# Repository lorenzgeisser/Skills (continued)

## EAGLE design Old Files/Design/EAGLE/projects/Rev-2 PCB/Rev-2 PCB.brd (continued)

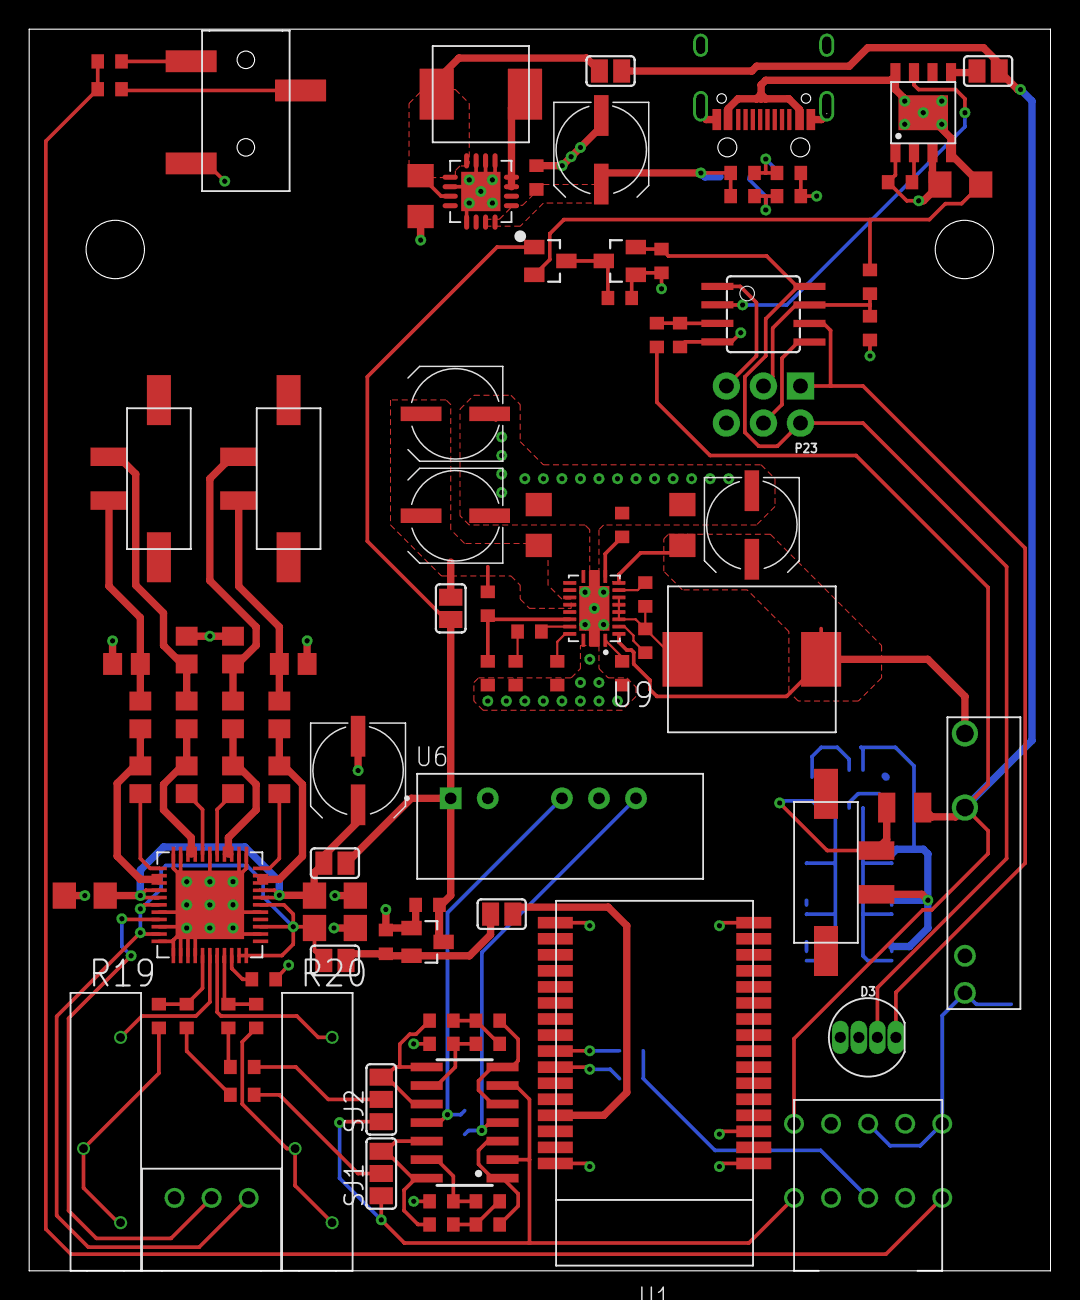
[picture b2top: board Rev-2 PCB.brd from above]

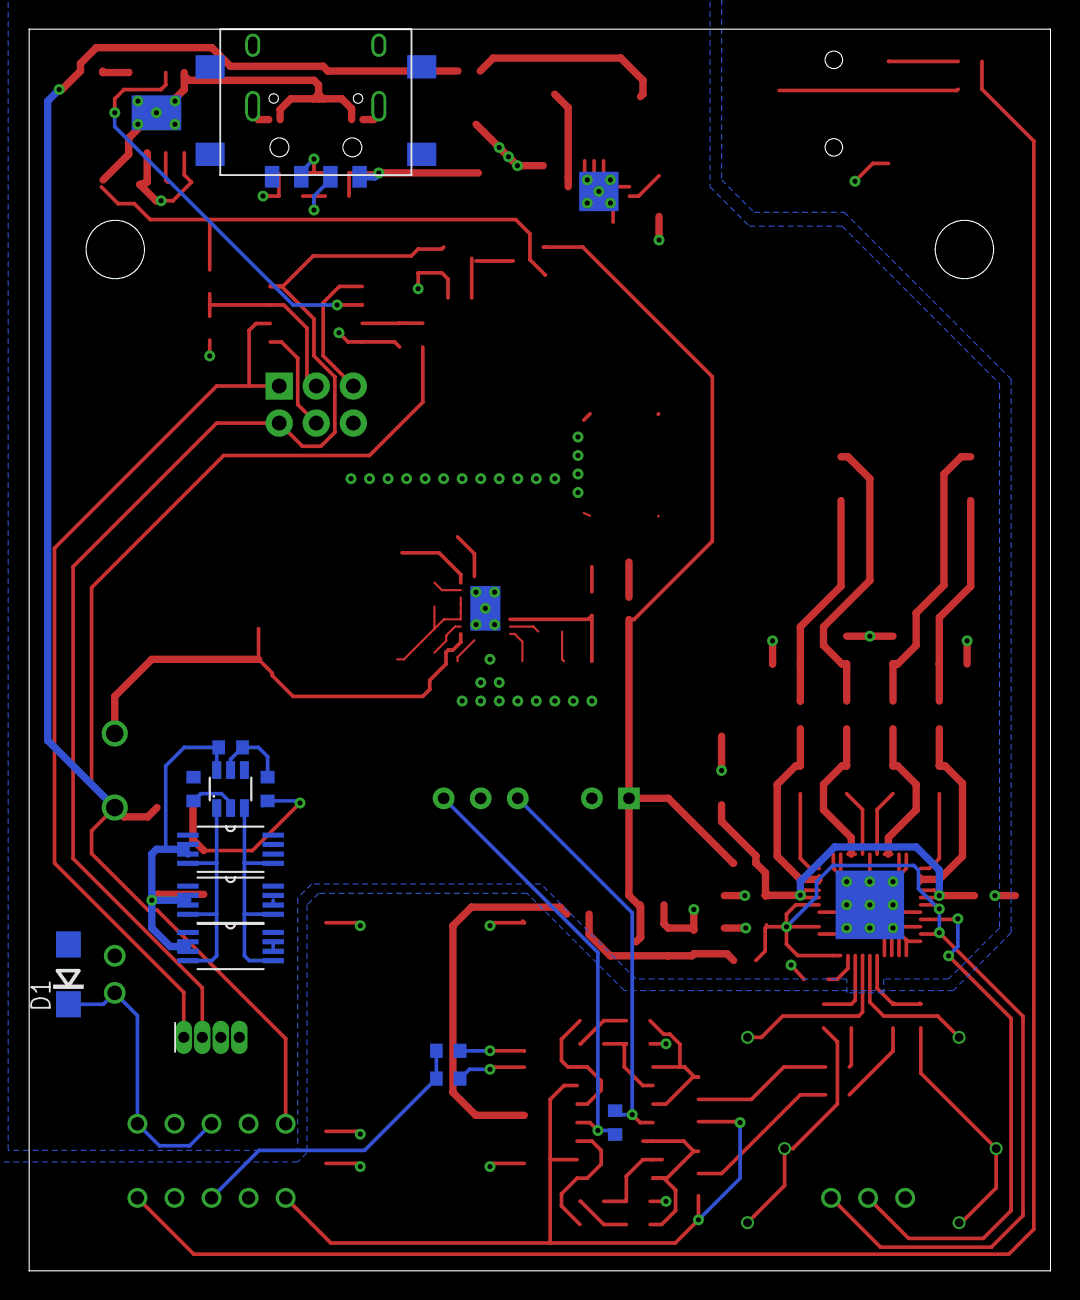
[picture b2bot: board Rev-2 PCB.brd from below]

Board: 2 copper layers, 70.0 x 85.1 mm, 110 parts (12 on the bottom side), 82 nets.

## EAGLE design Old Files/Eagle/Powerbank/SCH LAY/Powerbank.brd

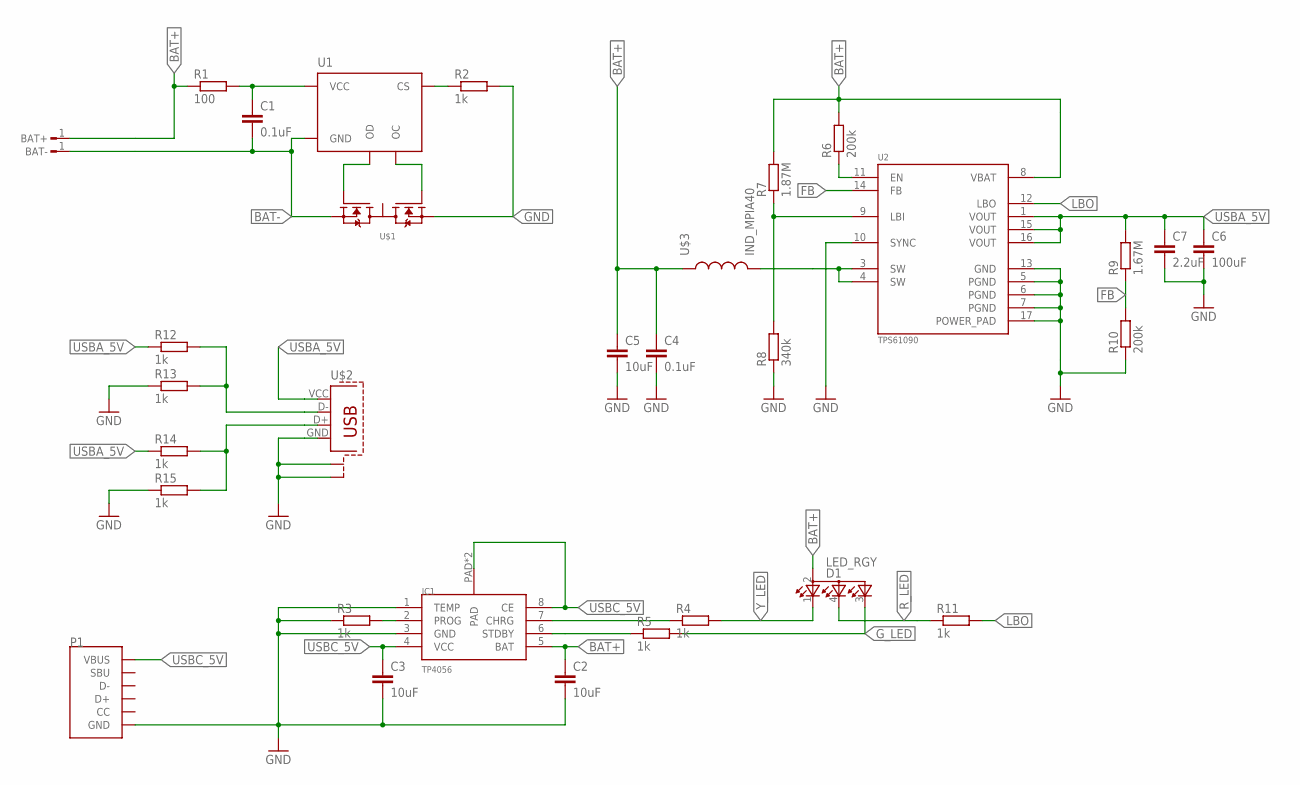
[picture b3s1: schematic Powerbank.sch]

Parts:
BAT+: SOLDER_PAD
BAT-: SOLDER_PAD
C1, C4: 0.1uF; C0805
C2, C3, C5: 10uF; C0805
C6: 100uF; C1210
C7: 2.2uF; C0805
D1: LED_RGY
IC1: TP4056; SOP-8
P1: TYPE-C
R1: 100; R0805
R2, R3, R4, R5, R11, R12, R13, R14, R15: 1k; R0805
R6, R10: 200k; R0805
R7: 1.87M; R0805
R8: 340k; R0805
R9: 1.67M; R0805
U1: FS312F; TSOT23-6
U2: TPS61090; QFN65P400X400X100-17N
U$1: FS8205; SOP65P640X120-8N
U$2: USB_A_SMD_U
U$3: IND_MPIA40

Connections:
BAT+: BAT+.1, C2.1, C4.1, C5.1, D1.2 (A), IC1.5 (BAT), R1.1, R6.2, R7.2, U2.8 (VBAT), U$3.P$1 (1)
BAT-: BAT-.1, C1.2, U1.6 (GND), U$1.2 (S1), U$1.3 (S1)
FB: R9.1, R10.2, U2.14 (FB)
GND: C2.2, C3.2, C4.2, C5.2, C6.2, C7.2, IC1.1 (TEMP), IC1.3 (GND), P1.A1/B12 (GND), P1.B1/A12 (GND), P1.P$1 (GND), P1.P$2 (GND), P1.P$3 (GND), P1.P$4 (GND), P1.P$5 (GND), P1.P$6 (GND), P1.P$7 (GND), P1.P$8 (GND), P1.P$9 (GND), P1.P$10 (GND), P1.P$11 (GND), P1.P$12 (GND), P1.P$13 (GND), P1.P$14 (GND), P1.P$15 (GND), P1.P$16 (GND), P1.P$17 (GND), P1.P$18 (GND), P1.P$19 (GND), P1.P$20 (GND), P1.P$21 (GND), P1.P$22 (GND), P1.P$23 (GND), P1.P$24 (GND), P1.P$25 (GND), P1.P$26 (GND), P1.P$27 (GND), P1.P$28 (GND), P1.P$29 (GND), P1.P$30 (GND), P1.P$31 (GND), P1.P$32 (GND), P1.P$33 (GND), P1.P$34 (GND), P1.P$35 (GND), P1.P$36 (GND), P1.P$37 (GND), P1.P$38 (GND), R2.2, R3.1, R8.1, R10.1, R13.1, R15.1, U2.5 (PGND), U2.6 (PGND), U2.7 (PGND), U2.10 (SYNC), U2.13 (GND), U2.17 (POWER_PAD), U$1.6 (S2), U$1.7 (S2), U$2.GND (4), U$2.P$2 (S1), U$2.P$6 (S2)
G_LED: D1.3 (GREEN), R5.2
LBO: R11.2, U2.12 (LBO)
unnamed: C1.1, R1.2, U1.5 (VCC)
unnamed: IC1.2 (PROG), R3.2
unnamed: IC1.7 (CHRG), R4.1
unnamed: U1.1 (OD), U$1.4 (G1)
unnamed: U1.3 (OC), U$1.5 (G2)
unnamed: R2.1, U1.2 (CS)
unnamed: IC1.6 (STDBY), R5.1
unnamed: R6.1, U2.11 (EN)
unnamed: U2.3 (SW), U2.4 (SW), U$3.P$2 (2)
unnamed: R7.1, R8.2, U2.9 (LBI)
unnamed: R14.2, R15.2, U$2.D+ (3)
unnamed: R12.2, R13.2, U$2.D- (2)
R_LED: D1.4 (YELLOW), R11.1
USBA_5V: C6.1, C7.1, R9.2, R12.1, R14.1, U2.1 (VOUT), U2.15 (VOUT), U2.16 (VOUT), U$2.VCC (1)
USBC_5V: C3.1, IC1.4 (VCC), IC1.8 (CE), IC1.PAD, IC1.PAD2 (PAD), P1.A4/B9 (VBUS), P1.B4/A9 (VBUS)
Y_LED: D1.1 (RED), R4.2

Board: 2 copper layers, 32 parts (0 on the bottom side), 22 nets, no tracks yet.

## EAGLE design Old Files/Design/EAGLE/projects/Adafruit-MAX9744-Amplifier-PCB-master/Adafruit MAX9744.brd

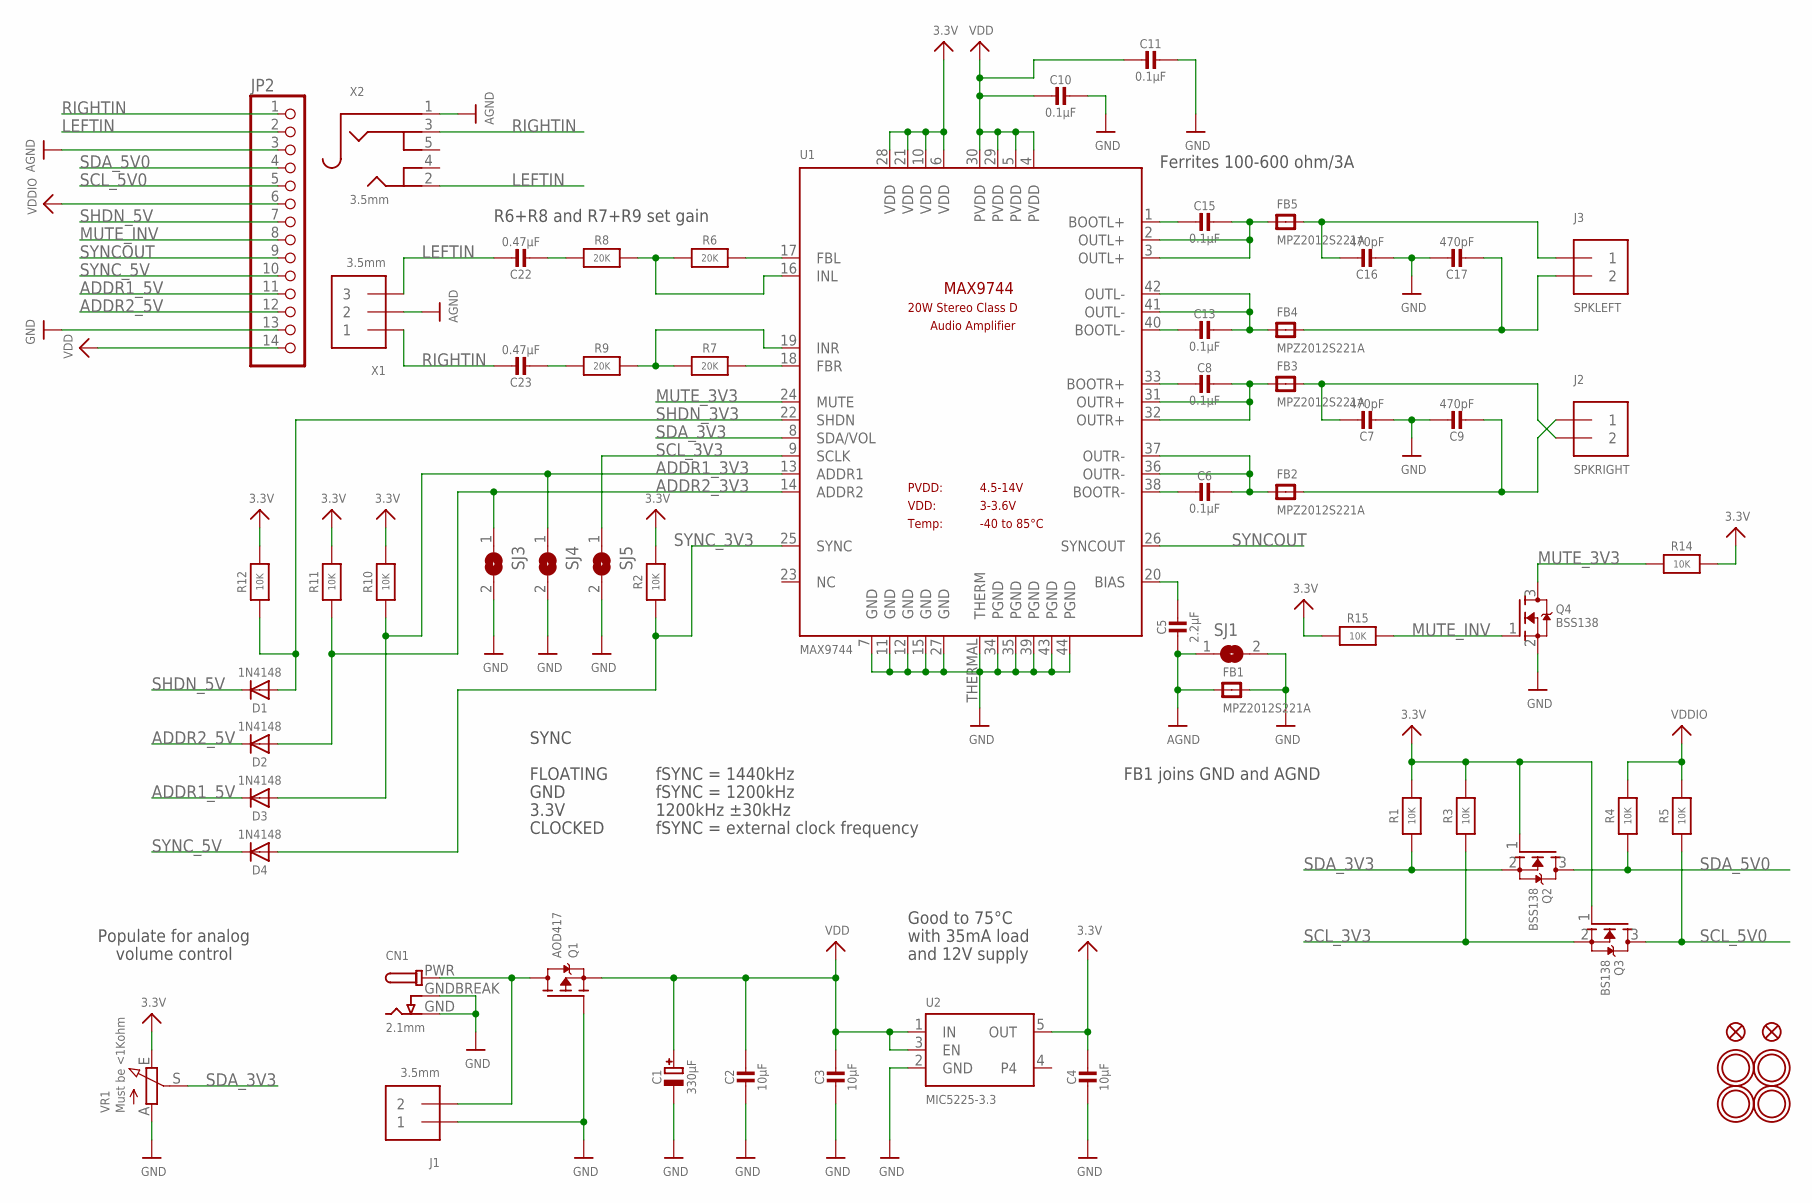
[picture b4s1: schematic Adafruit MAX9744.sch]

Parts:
C1: 330µF; CELEC_3.5MM_8MM
C2, C3, C4: 10µF; 0805-NO
C5: 2.2µF; 0805-NO
C6, C8, C10, C11, C13, C15: 0.1µF; 0805-NO
C7, C9, C16, C17: 470pF; 0805-NO
C22, C23: 0.47µF; 0805-NO
CN1: 2.1mm; DCJACK_2MM_SMT
D1, D2, D3, D4: 1N4148; SOD-323
FB1, FB2, FB3, FB4, FB5: MPZ2012S221A; _0805
FID1, FID2: FIDUCIAL""; FIDUCIAL_1MM
J1: 3.5mm; TERMBLOCK_1X2-3.5MM
J2: SPKRIGHT; TERMBLOCK_1X2-3.5MM
J3: SPKLEFT; TERMBLOCK_1X2-3.5MM
JP2: HEADER-1X14; 1X14_ROUND70
Q1: AOD417; TO252
Q2, Q4: BSS138; SOT23-WIDE
Q3: BS138; SOT23-WIDE
R1, R3, R4, R5, R12: 10K; 0805-NO
R2, R10, R11, R14, R15: 10K; _0805MP
R6, R7, R8, R9: 20K; 0805-NO
SJ1, SJ3, SJ4, SJ5: SOLDERJUMPER; SOLDERJUMPER_ARROW_NOPASTE
U1: MAX9744; TQFN44_7MM
U2: MIC5225-3.3; SOT23-5
U$29, U$38, U$39, U$40: MOUNTINGHOLE2.5_THICK; MOUNTINGHOLE_2.5_PLATED_THICK
VR1: Must be <1Kohm; TRIMPOT_100MILPTH
X1: 3.5mm; TERMBLOCK_1X3-3.5MM
X2: 3.5mm; 4UCONN_19269

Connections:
3.3V: C4.1, Q2.1 (G), Q3.1 (G), R1.2, R2.2, R3.2, R10.2, R11.2, R12.2, R14.2, R15.1, U1.6 (VDD), U1.10 (VDD), U1.21 (VDD), U1.28 (VDD), U2.5 (OUT), VR1.E
ADDR1_3V3: D3.A, R10.1, SJ4.1, U1.13 (ADDR1)
ADDR1_5V: D3.C, JP2.11
ADDR2_3V3: D2.A, R11.1, SJ3.1, U1.14 (ADDR2)
ADDR2_5V: D2.C, JP2.12
AGND: C5.2, FB1.1, JP2.3, SJ1.1, X1.2, X2.1
GND: C1.-, C2.2, C3.2, C4.2, C7.2, C9.1, C10.1, C11.1, C16.2, C17.1, CN1.GND, CN1.GNDBREAK, FB1.2, J1.1, JP2.13, Q1.1 (G), Q4.2 (S), SJ1.2, SJ3.2, SJ4.2, SJ5.2, U1.7 (GND), U1.11 (GND), U1.12 (GND), U1.15 (GND), U1.27 (GND), U1.34 (PGND), U1.35 (PGND), U1.39 (PGND), U1.43 (PGND), U1.44 (PGND), U1.THERMAL (THERM), U2.2 (GND), VR1.A
LEFTIN: C22.1, JP2.2, X1.3, X2.2
MUTE_3V3: Q4.3 (D), R14.1, U1.24 (MUTE)
MUTE_INV: JP2.8, Q4.1 (G), R15.2
unnamed: CN1.PWR, J1.2, Q1.3 (D)
unnamed: C5.1, U1.20 (BIAS)
unnamed: C6.2, U1.38 (BOOTR-)
unnamed: C6.1, FB2.1, U1.36 (OUTR-), U1.37 (OUTR-)
unnamed: C8.2, U1.33 (BOOTR+)
unnamed: C8.1, FB3.1, U1.31 (OUTR+), U1.32 (OUTR+)
unnamed: C7.1, FB3.2, J2.2
unnamed: C9.2, FB2.2, J2.1
unnamed: C13.1, FB4.1, U1.41 (OUTL-), U1.42 (OUTL-)
unnamed: C15.1, FB5.1, U1.2 (OUTL+), U1.3 (OUTL+)
unnamed: C16.1, FB5.2, J3.1
unnamed: C17.2, FB4.2, J3.2
unnamed: C15.2, U1.1 (BOOTL+)
unnamed: C13.2, U1.40 (BOOTL-)
unnamed: R6.2, U1.17 (FBL)
unnamed: R7.2, U1.18 (FBR)
unnamed: R6.1, R8.2, U1.16 (INL)
unnamed: R7.1, R9.2, U1.19 (INR)
unnamed: C22.2, R8.1
unnamed: C23.2, R9.1
RIGHTIN: C23.1, JP2.1, X1.1, X2.3
SCL_3V3: Q3.2 (S), R3.1, SJ5.1, U1.9 (SCLK)
SCL_5V0: JP2.5, Q3.3 (D), R5.1
SDA_3V3: Q2.2 (S), R1.1, U1.8 (SDA/VOL), VR1.S
SDA_5V0: JP2.4, Q2.3 (D), R4.1
SHDN_3V3: D1.A, R12.1, U1.22 (SHDN)
SHDN_5V: D1.C, JP2.7
SYNCOUT: JP2.9, U1.26 (SYNCOUT)
SYNC_3V3: D4.A, R2.1, U1.25 (SYNC)
SYNC_5V: D4.C, JP2.10
VDD: C1.+, C2.1, C3.1, C10.2, C11.2, JP2.14, Q1.2 (S), U1.4 (PVDD), U1.5 (PVDD), U1.29 (PVDD), U1.30 (PVDD), U2.1 (IN), U2.3 (EN)
VDDIO: JP2.6, R4.2, R5.2

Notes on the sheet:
Good to 75°C
with 35mA load
and 12V supply
FB1 joins GND and AGND
SYNC
FLOATING
GND
3.3V
CLOCKED
fSYNC = 1200kHz
fSYNC = 1440kHz
1200kHz ±30kHz
fSYNC = external clock frequency
R6+R8 and R7+R9 set gain
Ferrites 100-600 ohm/3A
Populate for analog
volume control

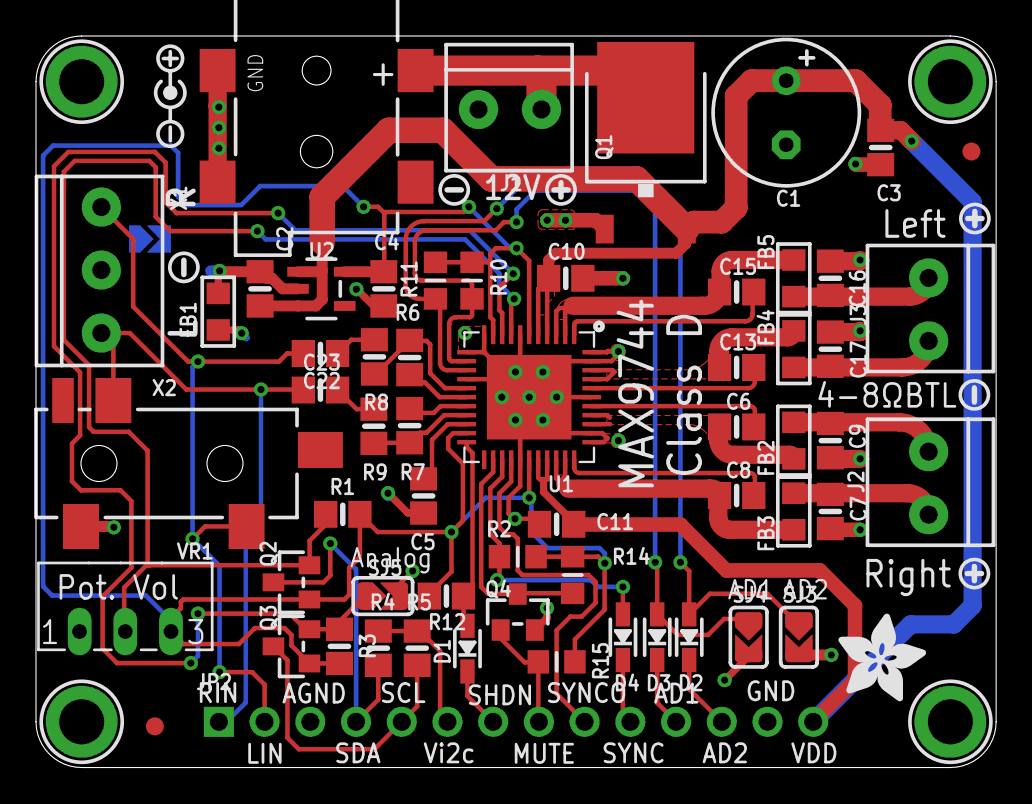
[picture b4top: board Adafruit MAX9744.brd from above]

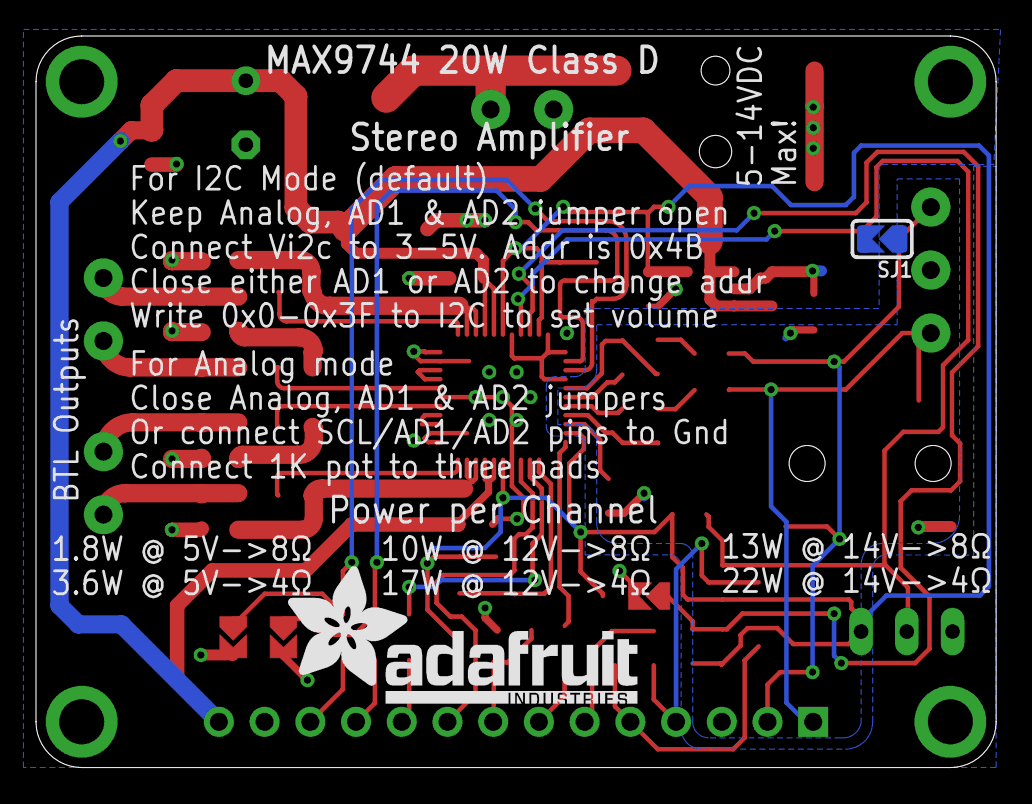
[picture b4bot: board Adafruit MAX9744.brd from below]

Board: 2 copper layers, 53.3 x 40.6 mm, 73 parts (2 on the bottom side), 42 nets.

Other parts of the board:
U$28: ADAFRUIT_TEXT_20MM
U$32: ADAFRUIT_5MM
U$41: ICON_POSITIVE_CENTER-M
U$42, U$50, U$52: ICON_PLUS
U$43, U$47, U$51: ICON_MINUS

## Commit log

2019-10-21 first
2019-10-21 in progress
2019-12-18 working
2019-12-23 restart
2019-12-23 new project
2020-01-09 changed plane
2020-01-10 add KicCad logo
2020-01-12 annotate
2020-01-13 gerber
2020-03-05 kain plan wa da söll
2020-06-02 work in progress
